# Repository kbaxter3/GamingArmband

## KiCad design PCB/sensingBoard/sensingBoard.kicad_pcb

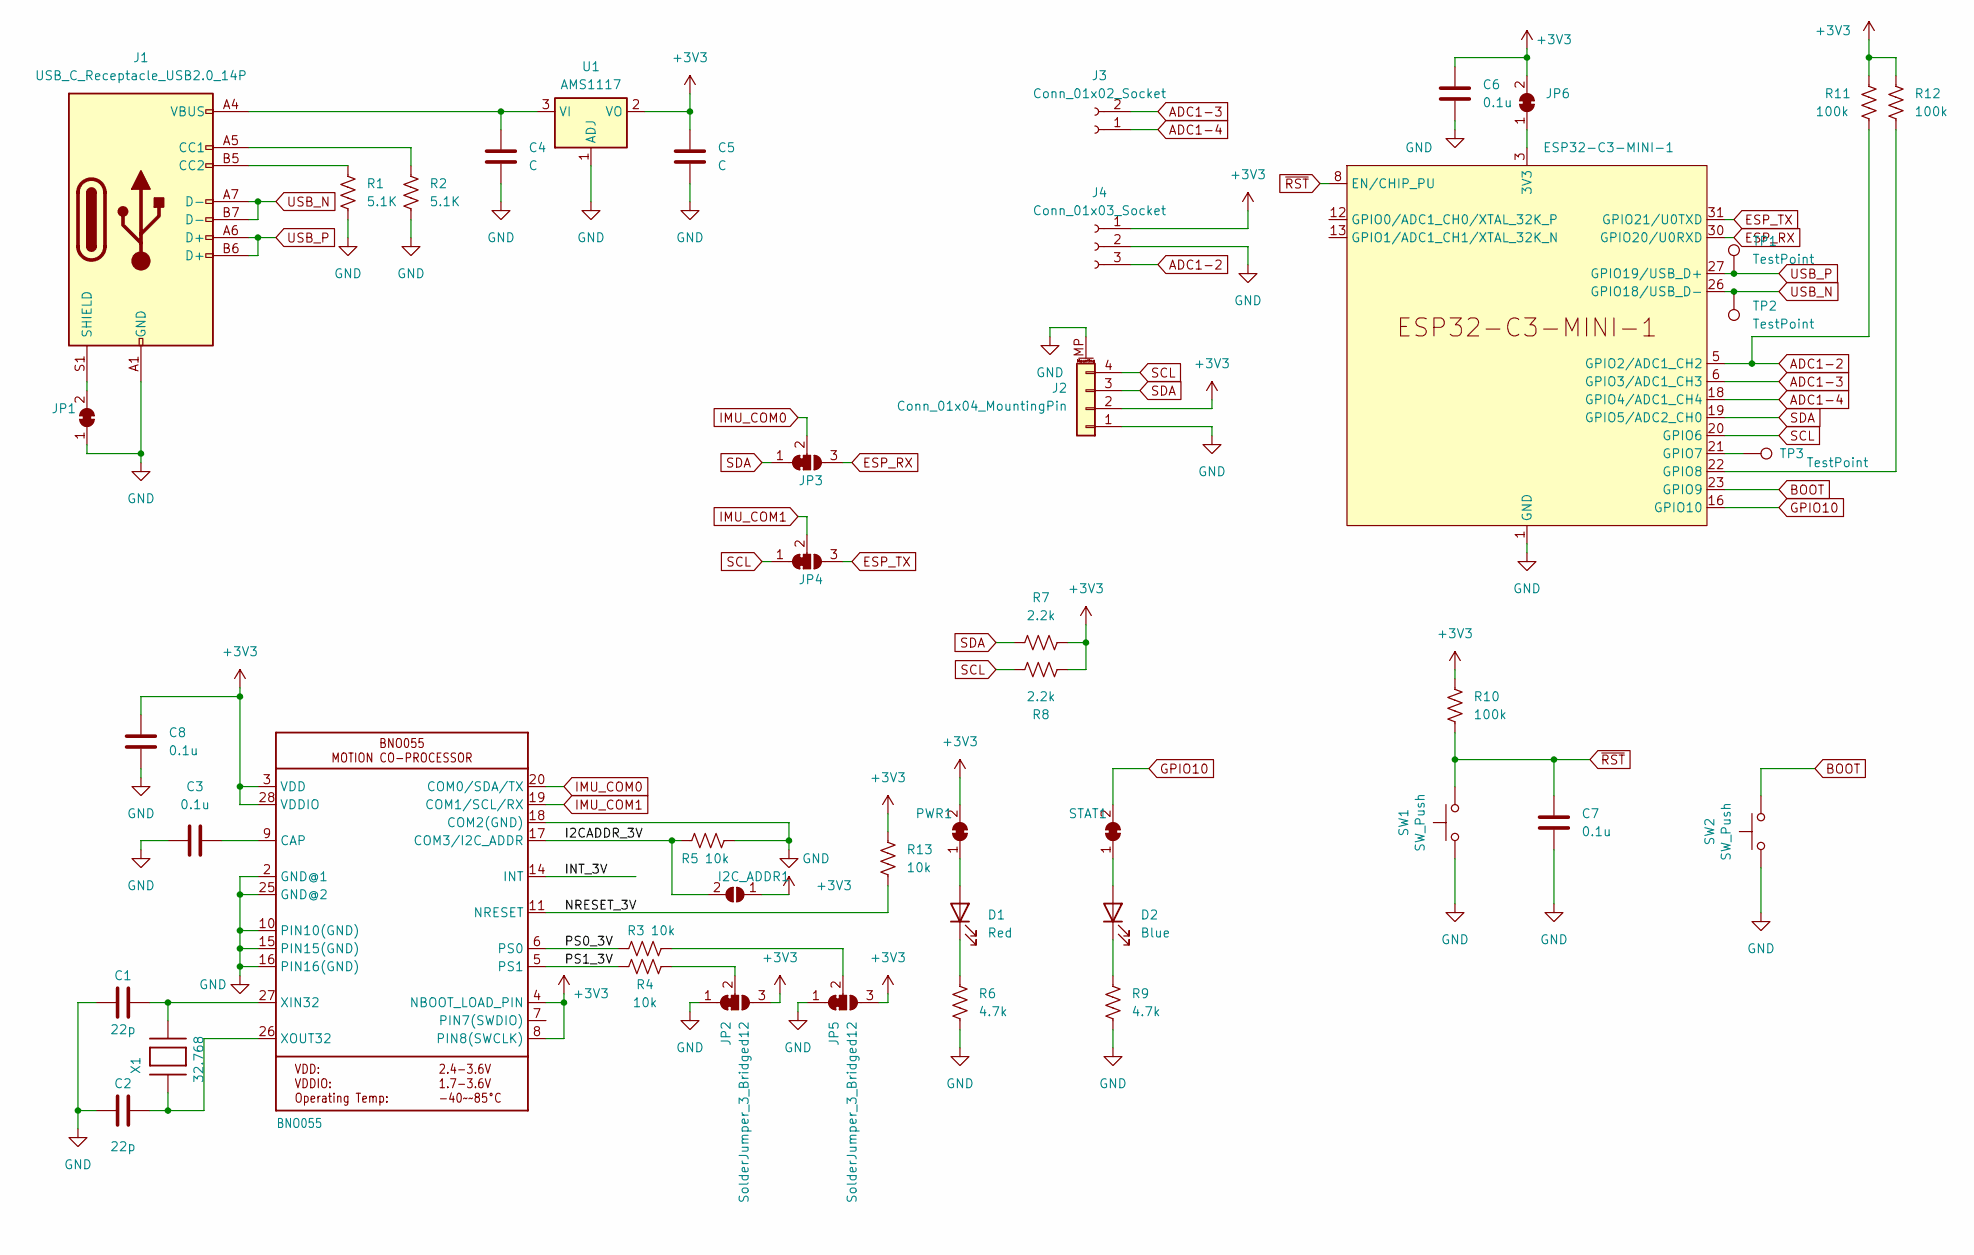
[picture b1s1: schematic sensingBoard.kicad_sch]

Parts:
C1, C2: 22p; C_0805_2012Metric_Pad1.18x1.45mm_HandSolder
C3, C6, C7, C8: 0.1u; C_0805_2012Metric_Pad1.18x1.45mm_HandSolder
C4, C5: C; C_0805_2012Metric_Pad1.18x1.45mm_HandSolder
D1: Red; LED_0805_2012Metric_Pad1.15x1.40mm_HandSolder
D2: Blue; LED_0805_2012Metric_Pad1.15x1.40mm_HandSolder
I2C_ADDR1: SolderJumper-2_P1.3mm_Open_RoundedPad1.0x1.5mm
J1: USB_C_Receptacle_USB2.0_14P; USB_C_Receptacle_GCT_USB4105-xx-A_16P_TopMnt_Horizontal
J2: Conn_01x04_MountingPin; JST_SH_BM04B-SRSS-TB_1x04-1MP_P1.00mm_Vertical
J3: Conn_01x02_Socket; PinSocket_1x02_P2.54mm_Vertical
J4: Conn_01x03_Socket; PinSocket_1x03_P2.54mm_Vertical
JP1, JP6: SolderJumper-2_P1.3mm_Bridged_RoundedPad1.0x1.5mm
JP2, JP3, JP4, JP5: SolderJumper_3_Bridged12; SolderJumper-3_P1.3mm_Bridged12_RoundedPad1.0x1.5mm
PWR1: SolderJumper-2_P1.3mm_Bridged_RoundedPad1.0x1.5mm
R1, R2: 5.1K; R_0805_2012Metric_Pad1.20x1.40mm_HandSolder
R3, R4, R5, R13: 10k; R_0805_2012Metric_Pad1.20x1.40mm_HandSolder
R6, R9: 4.7k; R_0805_2012Metric_Pad1.20x1.40mm_HandSolder
R7, R8: 2.2k; R_0805_2012Metric_Pad1.20x1.40mm_HandSolder
R10, R11, R12: 100k; R_0805_2012Metric_Pad1.20x1.40mm_HandSolder
STAT1: SolderJumper-2_P1.3mm_Bridged_RoundedPad1.0x1.5mm
SW1, SW2: SW_Push; SMD_Pushbutton_3mmx4mm
TP1, TP2, TP3: TestPoint; TestPoint_Pad_D1.0mm
U1: AMS1117; SOT-223-3_TabPin2
U2: ESP32-C3-MINI-1
U$1: BNO055
X1: 32.768; XTAL3215

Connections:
+3V3: C5.1, C6.1, C8.1, I2C_ADDR1.1 (A), J2.2, J4.1, JP2.3 (B), JP5.3 (B), JP6.2 (B), PWR1.2 (B), R7.2, R8.1, R10.1, R11.1, R12.1, R13.1, U1.2 (VO), U$1.3 (VDD), U$1.4 (NBOOT_LOAD_PIN), U$1.8 (PIN8(SWCLK)), U$1.28 (VDDIO)
/I2CADDR_3V: I2C_ADDR1.2 (B), R5.1, U$1.17 (COM3/I2C_ADDR)
/INT_3V: U$1.14 (INT)
/NRESET_3V: R13.2, U$1.11 (NRESET)
/PS0_3V: R3.1, U$1.6 (PS0)
/PS1_3V: R4.1, U$1.5 (PS1)
ADC1-2: J4.3, R11.2, U2.5 (GPIO2/ADC1_CH2)
ADC1-3: J3.2, U2.6 (GPIO3/ADC1_CH3)
ADC1-4: J3.1, U2.18 (GPIO4/ADC1_CH4)
BOOT: SW2.2, U2.23 (GPIO9)
ESP_RX: JP3.3 (B), U2.30 (GPIO20/U0RXD)
ESP_TX: JP4.3 (B), U2.31 (GPIO21/U0TXD)
GND: C1.1, C2.1, C3.1, C4.2, C5.2, C6.2, C7.2, C8.2, J1.A1 (GND), J1.A12 (GND), J1.B1 (GND), J1.B12 (GND), J2.1, J2.MP (MountPin), J4.2, JP1.1 (A), JP2.1 (A), JP5.1 (A), R1.2, R2.2, R5.2, R6.2, R9.2, SW1.1, SW2.1, U1.1 (ADJ), U2.1 (GND), U2.2 (GND), U2.11 (GND), U2.14 (GND), U2.36 (GND), U2.37 (GND), U2.38 (GND), U2.39 (GND), U2.40 (GND), U2.41 (GND), U2.42 (GND), U2.43 (GND), U2.44 (GND), U2.45 (GND), U2.46 (GND), U2.47 (GND), U2.48 (GND), U2.49 (GND), U2.50 (GND), U2.51 (GND), U2.52 (GND), U2.53 (GND), U$1.2 (GND@1), U$1.10 (PIN10(GND)), U$1.15 (PIN15(GND)), U$1.16 (PIN16(GND)), U$1.18 (COM2(GND)), U$1.25 (GND@2)
GPIO10: STAT1.2 (B), U2.16 (GPIO10)
IMU_COM0: JP3.2 (C), U$1.20 (COM0/SDA/TX)
IMU_COM1: JP4.2 (C), U$1.19 (COM1/SCL/RX)
unnamed: D1.2 (A), PWR1.1 (A)
unnamed: D1.1 (K), R6.1
unnamed: D2.2 (A), STAT1.1 (A)
unnamed: D2.1 (K), R9.1
unnamed: J1.A5 (CC1), R2.1
unnamed: J1.B5 (CC2), R1.1
unnamed: J1.S1 (SHIELD), JP1.2 (B)
unnamed: JP2.2 (C), R4.2
unnamed: JP5.2 (C), R3.2
unnamed: JP6.1 (A), U2.3 (3V3)
unnamed: C4.1, J1.A4 (VBUS), J1.A9 (VBUS), J1.B4 (VBUS), J1.B9 (VBUS), U1.3 (VI)
unnamed: TP3.1, U2.21 (GPIO7)
unnamed: R12.2, U2.22 (GPIO8)
unnamed: C3.2, U$1.9 (CAP)
unnamed: C1.2, U$1.27 (XIN32), X1.P$2
unnamed: C2.2, U$1.26 (XOUT32), X1.P$1
SCL: J2.4, JP4.1 (A), R8.2, U2.20 (GPIO6)
SDA: J2.3, JP3.1 (A), R7.1, U2.19 (GPIO5/ADC2_CH0)
USB_N: J1.A7 (D-), J1.B7 (D-), TP2.1, U2.26 (GPIO18/USB_D-)
USB_P: J1.A6 (D+), J1.B6 (D+), TP1.1, U2.27 (GPIO19/USB_D+)
~RST: C7.1, R10.2, SW1.2, U2.8 (EN/CHIP_PU)

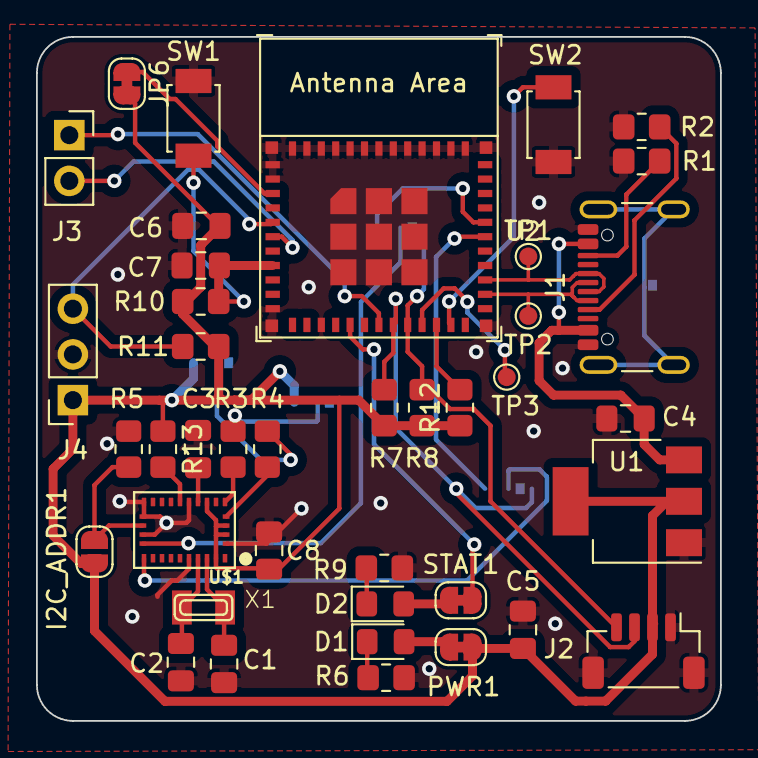
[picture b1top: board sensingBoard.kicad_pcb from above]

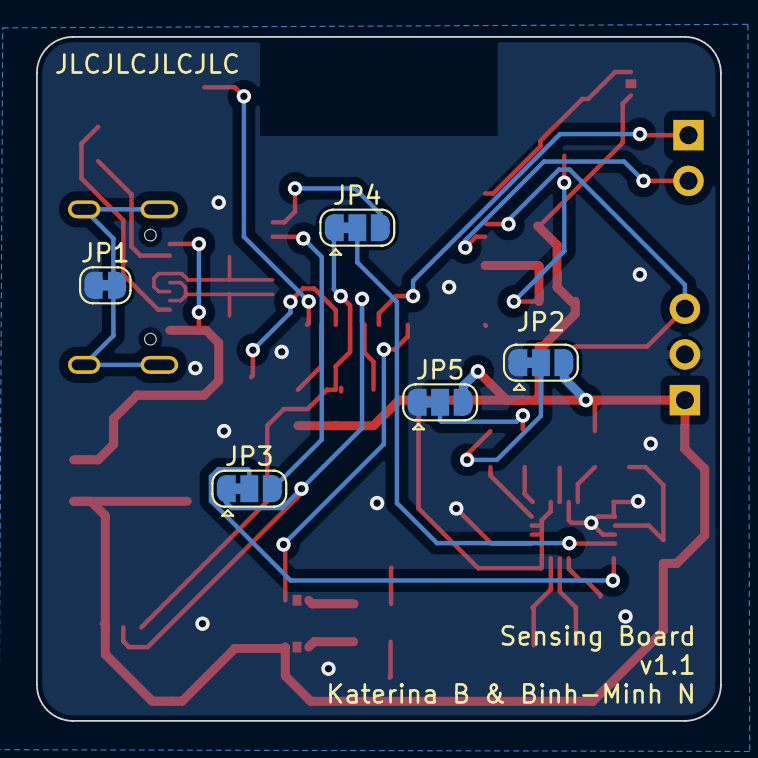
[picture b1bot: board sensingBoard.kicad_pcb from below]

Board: 2 copper layers, 38.0 x 38.0 mm, 45 parts (5 on the bottom side), 36 nets.

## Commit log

2024-03-02 Added PCB and created test code to collect data
2024-03-20 board v1
2024-03-24 modified sensor board and wrote firmware for wireless data transfer
2024-03-26 gitignore for kicad backup, added pullup for nreset on imu
2024-03-28 communication between ESP32 receiver and arduino
2024-04-02 up/down arrow w/ imu, started emg control, WIP
2024-04-02 implemented emg contol to turn on and off keyboard
2024-04-02 Implement barebones EMG graph
2024-04-02 Update EMG graph
2024-04-04 Added 3D Vector Graph and fixed EMG scaling issue
2024-04-04 adjusted emg control cutoffs and added sensor board firmware without serial
2024-04-05 commented out lines in receiverBoard to work with data visualization
2024-04-05 adjusted data visualization to use serial and chnaged receiverBoard to show EMG cuttoffs and signal
